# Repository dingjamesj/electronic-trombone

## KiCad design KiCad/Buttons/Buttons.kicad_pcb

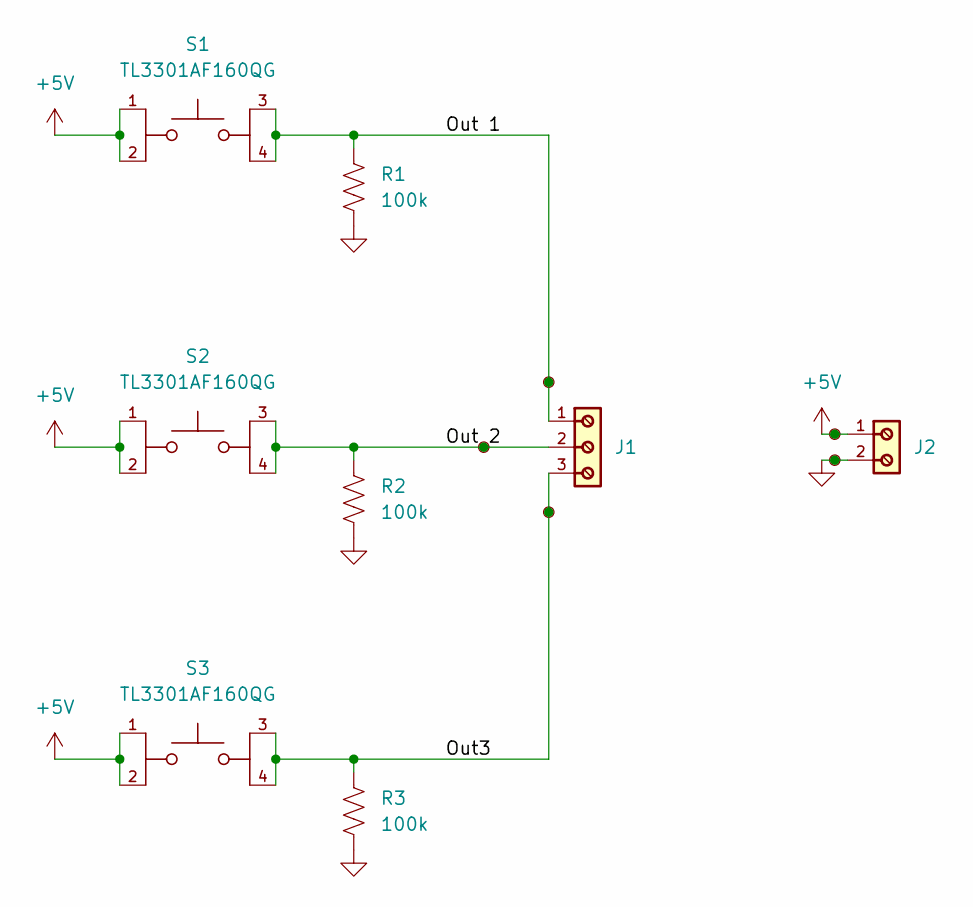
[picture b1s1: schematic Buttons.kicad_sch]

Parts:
J1: 691137710003
J2: 691137710002
R1, R2, R3: 100k; R_Axial_DIN0207_L6.3mm_D2.5mm_P7.62mm_Horizontal
S1, S2, S3: TL3301AF160QG; SW_TL3301AF160QG; PARTREV E
TP1, TP2, TP3, TP4, TP5: TestPoint_Small; TestPoint_Keystone_5000-5004_Miniature

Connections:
+5V: J2.1, S1.1, S1.2, S2.1, S2.2, S3.1, S3.2, TP2.1 (1_1)
/Out3: J1.3, R3.1, S3.3, S3.4, TP5.1 (1_1)
/Out 1: J1.1, R1.1, S1.3, S1.4, TP3.1 (1_1)
/Out 2: J1.2, R2.1, S2.3, S2.4, TP4.1 (1_1)
GND: J2.2, R1.2, R2.2, R3.2, TP1.1 (1_1)

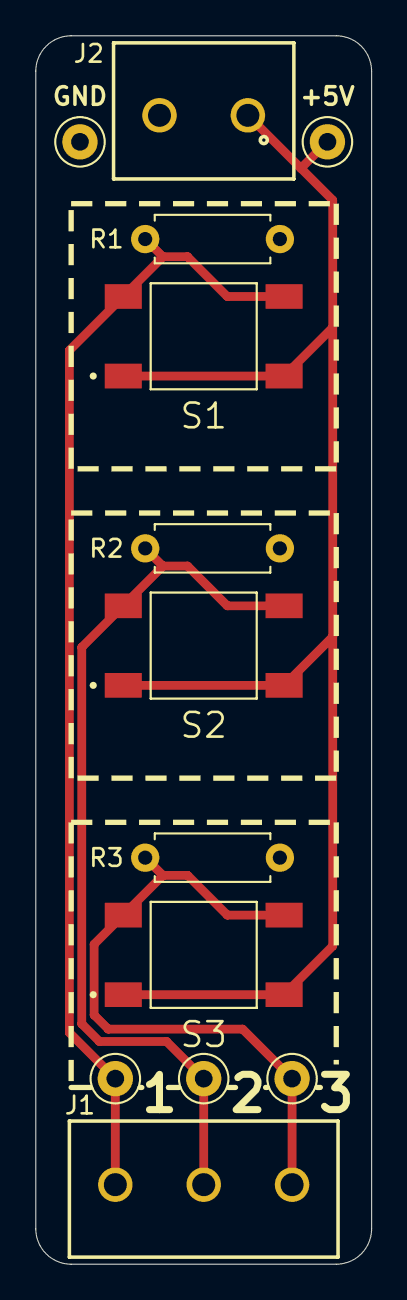
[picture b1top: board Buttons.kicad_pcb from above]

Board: 2 copper layers, 19.0 x 69.5 mm, 13 parts (0 on the bottom side), 5 nets.

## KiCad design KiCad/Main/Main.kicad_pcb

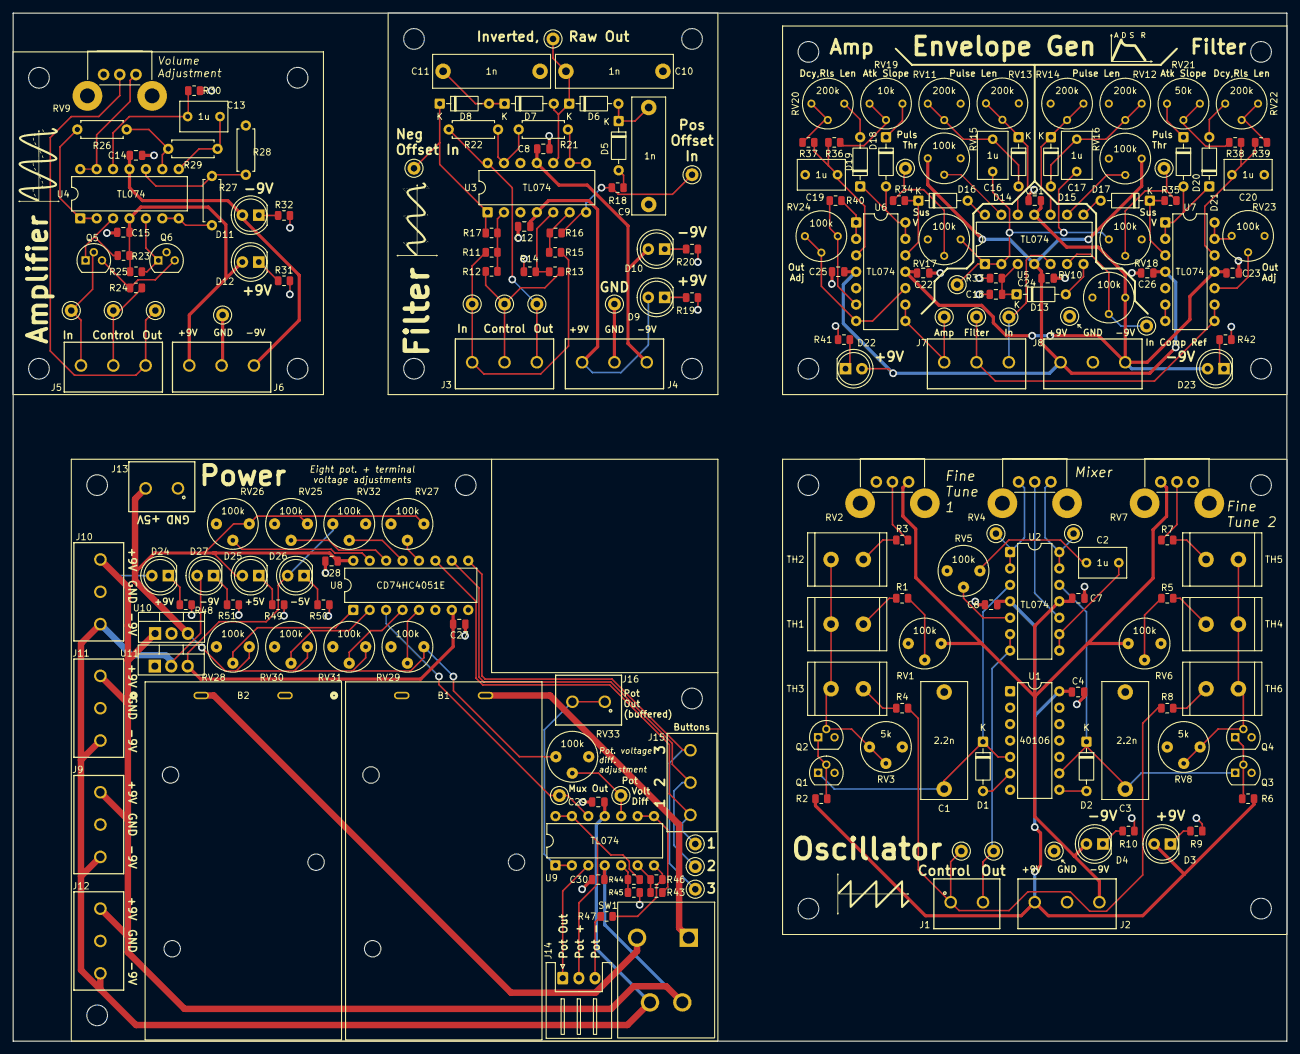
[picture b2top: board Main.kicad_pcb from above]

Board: 2 copper layers, 197.0 x 159.0 mm, 231 parts (0 on the bottom side), 127 nets.

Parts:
B1, B2: BC9VPC; BC9VPC_MPD
C1, C3: 2.2n; C_Rect_L18.0mm_W7.0mm_P15.00mm_FKS3_FKP3
C2, C13, C16, C17, C19, C20: 1u; C_Rect_L7.2mm_W4.5mm_P5.00mm
C4, C6, C7, C8, C12, C14, C15, C21, C22, C23, C24, C25, C26, C27, C28, C29, C30: 0.1u; C_0805_2012Metric
C9, C10, C11: 1n; C_Rect_L18.0mm_W5.0mm_P15.00mm_FKS3_FKP3
C18: 10n; C_0805_2012Metric
D1, D2, D5, D6, D7, D8, D13, D14, D15, D16, D17, D18, D19, D20, D21: 1N4148; D_DO-35_SOD27_P7.62mm_Horizontal
D3, D4, D9, D10, D11, D12, D22, D23, D24, D25, D26, D27: LED; LED_D5.0mm
H1, H2, H3, H4: MountingHole_3.2mm_M3
H5, H6, H7, H8, H9, H10, H11, H12, H13, H14, H15, H16, H17, H18, H19, H20: MountingHole; MountingHole_3.2mm_M3
J1, J13, J16: Screw_Terminal_01x02; 691137710002
J2, J3, J4, J5, J6, J7, J8, J9, J10, J11, J12, J15: Screw_Terminal_01x03; 691137710003
J14: Conn_01x03; JST_XH_S3B-XH-A_1x03_P2.50mm_Horizontal
Q1, Q3, Q5, Q6: NPN; TO-92
Q2, Q4: PNP; TO-92
R1, R4, R5, R8, R23, R25, R30, R33, R34, R35: 100k; R_0805_2012Metric
R2, R3, R6, R7: 1M; R_0805_2012Metric
R9, R10, R19, R20, R31, R32, R36, R41, R42, R47, R48, R51: 1k; R_0805_2012Metric
R11, R12, R13, R14, R15, R16, R17, R24, R43, R44, R45, R46: 10k; R_0805_2012Metric
R18: 2.2k; R_0805_2012Metric
R21, R28, R29: 10k; R_Axial_DIN0207_L6.3mm_D2.5mm_P7.62mm_Horizontal
R22: 1k; R_Axial_DIN0207_L6.3mm_D2.5mm_P7.62mm_Horizontal
R26, R27: 2.7k; R_Axial_DIN0207_L6.3mm_D2.5mm_P7.62mm_Horizontal
R37, R39, R40: 51k; R_0805_2012Metric
R38: 22k; R_0805_2012Metric
R49, R50: 820; R_0805_2012Metric
RV1, RV5, RV6, RV25, RV26, RV27, RV28, RV29, RV30, RV31, RV32, RV33: 100k; Potentiometer_Bourns_3339P_Vertical_HandSoldering
RV2, RV4, RV7, RV9: 100k; Potentiometer_Bourns_PTV09A-2_Single_Horizontal
RV3, RV8: 5k; Potentiometer_Bourns_3339P_Vertical_HandSoldering
RV10, RV15, RV16, RV17, RV18, RV23, RV24: 100k; Potentiometer_Bourns_3339P_Vertical
RV11, RV12, RV13, RV14, RV20, RV22: 200k; Potentiometer_Bourns_3339P_Vertical
RV19: 10k; Potentiometer_Bourns_3339P_Vertical
RV21: 50k; Potentiometer_Bourns_3339P_Vertical
SW1: SW_DPST; DPST Switch RA83231100
TH1, TH2, TH3, TH4, TH5, TH6: 10k; R_Radial_Power_L12.0mm_W8.0mm_P5.00mm
TP1, TP2, TP3, TP4, TP5, TP6, TP7, TP8, TP9, TP10, TP11, TP12, TP13, TP14, TP15, TP16, TP17, TP18, TP19, TP20, TP21, TP22, TP23, TP24, TP25, TP26, TP27, TP28, TP29: TestPoint_Small; TestPoint_Keystone_5000-5004_Miniature
U1: 40106; DIP-14_W7.62mm
U2, U3, U4, U5, U6, U7, U9: TL074; DIP-14_W7.62mm
U8: CD74HC4051E; DIP-16_W7.62mm
U10: L7805; TO-220-3_Vertical
U11: L7905; TO-220-3_Vertical

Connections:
+5V: C28.2, D25.2 (A), J13.2, RV25.1, RV26.1, RV27.1, RV28.1, RV29.1, RV30.1, RV31.1, RV33.3, U8.16 (VCC), U10.3 (OUT)
+9V: C4.1, C6.1, C12.2, C15.2, C24.2, C25.2, C26.2, C30.2, D3.2 (A), D9.2 (A), D11.2 (A), D22.2 (A), D24.2 (A), J2.1, J4.1, J6.1, J8.1, J9.1, J10.1, J11.1, J12.1, R2.1, R6.1, R23.1, R25.1, RV15.3, RV16.1, SW1.2, U1.14 (VDD), U2.4 (V+), U3.4 (V+), U4.4 (V+), U5.4 (V+), U6.4 (V+), U7.4 (V+), U9.4 (V+), U10.1 (IN)
-5V: C27.1, D26.2 (A), RV32.3, U8.7 (VEE), U11.3 (VO)
-9V: C7.2, C8.1, C14.1, C21.1, C22.1, C23.1, C29.1, D4.2 (A), D10.2 (A), D12.2 (A), D23.2 (A), D27.2 (A), J2.3, J4.3, J6.3, J8.3, J9.3, J10.3, J11.3, J12.3, RV1.1, RV2.1, RV6.3, RV7.3, RV10.1, SW1.4, U2.11 (V-), U3.11 (V-), U4.11 (V-), U5.11 (V-), U6.11 (V-), U7.11 (V-), U9.11 (V-), U11.2 (VI)
/Buffered Inverted Raw Out: R21.1, U3.8, U3.9 (-)
/Buffered Pot Out: J16.1, J16.2, U9.1, U9.2 (-)
/Button 1: J15.1, TP25.1 (1_1), U8.11 (S0)
/Button 2: J15.2, TP26.1 (1_1), U8.10 (S1)
/Button 3: J15.3, TP27.1 (1_1), U8.9 (S2)
/Control: J3.2, J5.2, R12.1, R13.2, R24.2, TP7.1 (1_1), TP14.1 (1_1)
/Envelope Generator/Amp Burst: D16.2 (A), U5.14
/Envelope Generator/Amp Out: J7.1, TP21.1 (1_1), U6.8, U6.9 (-)
/Envelope Generator/Amp Sustain/Base Voltage: R34.2, RV17.2, TP19.1 (1_1)
/Envelope Generator/Amp Target Voltage: D18.2 (A), D19.1 (K), U6.13 (-), U6.14
/Envelope Generator/Filter Burst: D17.2 (A), U5.8
/Envelope Generator/Filter Out: J7.2, TP22.1 (1_1), U7.8, U7.9 (-)
/Envelope Generator/Filter Sustain/Base Voltage: R35.2, RV18.2, TP20.1 (1_1)
/Envelope Generator/Filter Target Voltage: D20.2 (A), D21.1 (K), U7.1, U7.2 (-)
/Envelope Generator/In: J7.3, TP23.1 (1_1), U5.5 (+)
/Envelope Generator/Input Comparator Ref: RV10.2, TP17.1 (1_1), U5.6 (-)
/Envelope Generator/Normalized In: C16.1, C17.1, RV17.1, RV18.3, TP18.1 (1_1), U5.1, U5.2 (-)
/Envelope Generator/Unscaled Amp Out: R40.1, U6.1, U6.2 (-)
/Envelope Generator/Unscaled Filter Out: RV23.3, U7.13 (-), U7.14
/In: J3.1, J5.1, Q5.2 (B), R11.1, R15.1, TP6.1 (1_1), TP13.1 (1_1)
/Inverted Raw Out: C10.2, D6.1 (K), D7.2 (A), TP12.1 (1_1), U3.10 (+)
/Mux Out: TP28.1 (1_1), U8.3 (A), U9.12 (+)
/Oscillator/Control: J1.1, R4.1, R8.1, TP3.1 (1_1)
/Oscillator/Mix In 1: RV4.3, TP1.1 (1_1), U2.1, U2.2 (-)
/Oscillator/Mix In 2: RV4.1, TP2.1 (1_1), U2.13 (-), U2.14
/Oscillator/Out: J1.2, TP4.1 (1_1), U2.6 (-), U2.7
/Oscillator/Processed Control 1: Q2.2 (B), RV3.2, RV3.3, TH1.2, TH2.2, TH3.2
/Oscillator/Processed Control 2: Q4.2 (B), RV8.1, RV8.2, TH4.2, TH5.2, TH6.2
/Oscillator/Sch Inv In 1: C1.1, D1.1 (K), Q1.1 (C), U1.5, U2.3 (+)
/Oscillator/Sch Inv In 2: C3.1, D2.1 (K), Q3.1 (C), U1.9, U2.12 (+)
/Oscillator/Sch Inv Out 1: D1.2 (A), U1.6
/Oscillator/Sch Inv Out 2: D2.2 (A), U1.8
/Out: J3.3, J5.3, R22.2, RV9.2, TP8.1 (1_1), TP15.1 (1_1), U3.14
/Pot +: J14.2, R44.1, U9.13 (-), U9.14
/Pot -: J14.3, R47.2
/Pot Out: J14.1, U9.3 (+)
/Pot Voltage Difference: RV33.2, TP29.1 (1_1), U9.10 (+)
/Pot+ 1st Partial: RV25.2, U8.14 (A1)
/Pot+ 2nd Partial: RV26.2, U8.15 (A2)
/Pot+ 3rd Partial: RV27.2, U8.12 (A3)
/Pot+ 4th Partial: RV28.2, U8.1 (A4)
/Pot+ 5th Partial: RV29.2, U8.5 (A5)
/Pot+ 6th Partial: RV30.2, U8.2 (A6)
/Pot+ 7th Partial: RV31.2, U8.4 (A7)
/Pot+ Inactive: RV32.2, U8.13 (A0)
/Power/Thaw 3: U7.6 (-), U7.7
/Signal w. + Offset: R16.2, R18.1, TP10.1 (1_1), U3.7
/Signal w. - Offset: D8.1 (K), R17.2, TP11.1 (1_1), U3.1
GND: B1.1, B2.2, C1.2, C3.2, C4.2, C6.2, C7.1, C8.2, C9.1, C10.1, C11.1, C12.1, C14.2, C15.1, C18.2, C19.1, C20.1, C21.2, C22.2, C23.2, C24.1, C25.1, C26.1, C27.2, C28.1, C29.2, C30.1, J2.2, J4.2, J6.2, J8.2, J9.2, J10.2, J11.2, J12.2, J13.1, Q1.3 (E), Q2.3 (E), Q3.3 (E), Q4.3 (E), Q6.2 (B), R9.2, R10.2, R14.1, R19.2, R20.2, R28.2, R30.2, R31.2, R32.2, R33.2, R41.2, R42.2, R45.1, R48.2, R49.2, R50.2, R51.2, RV1.3, RV2.3, RV3.1, RV5.3, RV6.1, RV7.1, RV8.3, RV9.3, RV10.3, RV11.1, RV12.3, RV13.1, RV14.3, RV15.1, RV16.3, RV17.3, RV18.1, RV23.1, RV25.3, RV26.3, RV27.3, RV28.3, RV29.3, RV30.3, RV31.3, RV32.1, RV33.1, TP5.1 (1_1), TP9.1 (1_1), TP16.1 (1_1), TP24.1 (1_1), U1.1, U1.3, U1.7 (VSS), U1.11, U1.13, U3.3 (+), U3.12 (+), U6.5 (+), U7.5 (+), U8.6 (*E), U8.8 (GND), U10.2 (GND), U11.1 (GND)
unnamed: B1.2, SW1.1
unnamed: B2.1, SW1.3
unnamed: C2.2, RV5.1
unnamed: C13.1, R29.2, U4.8
unnamed: D3.1 (K), R9.1
unnamed: D4.1 (K), R10.1
unnamed: D5.2 (A), R18.2
unnamed: C9.2, D5.1 (K), D6.2 (A)
unnamed: C11.2, D7.1 (K), D8.2 (A)
unnamed: D9.1 (K), R19.1
unnamed: D10.1 (K), R20.1
unnamed: D11.1 (K), R31.1
unnamed: D12.1 (K), R32.1
unnamed: D13.2 (A), U5.7
unnamed: C18.1, D13.1 (K), R33.1, U5.3 (+)
unnamed: C16.2, D14.2 (A), RV11.2, RV11.3
unnamed: D14.1 (K), RV13.2, RV13.3, U5.12 (+)
unnamed: C17.2, D15.2 (A), RV12.1, RV12.2
unnamed: D15.1 (K), RV14.1, RV14.2, U5.10 (+)
unnamed: D16.1 (K), R34.1, U6.12 (+)
unnamed: D17.1 (K), R35.1, U7.3 (+)
unnamed: D18.1 (K), RV19.1
unnamed: D19.2 (A), RV20.1
unnamed: D20.1 (K), RV21.3
unnamed: D21.2 (A), RV22.3
unnamed: D22.1 (K), R41.1
unnamed: D23.1 (K), R42.1
unnamed: D24.1 (K), R48.1
unnamed: D25.1 (K), R49.1
unnamed: D26.1 (K), R50.1
unnamed: D27.1 (K), R51.1
unnamed: Q1.2 (B), Q2.1 (C), R2.2
unnamed: Q3.2 (B), Q4.1 (C), R6.2
unnamed: Q5.1 (C), R23.2, U4.3 (+)
unnamed: Q5.3 (E), Q6.3 (E), R24.1
unnamed: Q6.1 (C), R25.2, U4.5 (+)
unnamed: R1.1, RV1.2
unnamed: R1.2, TH1.1
unnamed: R3.1, RV2.2
unnamed: R3.2, TH2.1
unnamed: R4.2, TH3.1
unnamed: R5.1, RV6.2
unnamed: R5.2, TH4.1
unnamed: R7.1, RV7.2
unnamed: R7.2, TH5.1
unnamed: R8.2, TH6.1
unnamed: R36.1, RV19.2, RV19.3
unnamed: R37.1, RV20.2, RV20.3
unnamed: R38.1, RV21.1, RV21.2
unnamed: R39.1, RV22.1, RV22.2
unnamed: R46.2, R47.1, U9.7
unnamed: RV5.2, U2.5 (+)
unnamed: RV4.2, U2.10 (+)
unnamed: C2.1, U2.8, U2.9 (-)
unnamed: R11.2, R12.2, R17.1, U3.2 (-)
unnamed: R13.1, R14.2, U3.5 (+)
unnamed: R15.2, R16.1, U3.6 (-)
unnamed: R21.2, R22.1, U3.13 (-)
unnamed: R26.1, U4.1, U4.2 (-)
unnamed: R27.1, U4.6 (-), U4.7
unnamed: R27.2, R28.1, U4.10 (+)
unnamed: R26.2, R29.1, U4.9 (-)
unnamed: C13.2, R30.1, U4.12 (+)
unnamed: RV9.1, U4.13 (-), U4.14
unnamed: RV16.2, U5.9 (-)
unnamed: RV15.2, U5.13 (-)
unnamed: C19.2, R36.2, R37.2, U6.3 (+)
unnamed: R40.2, RV24.1, U6.6 (-)
unnamed: RV24.2, RV24.3, U6.7, U6.10 (+)
unnamed: RV23.2, U7.10 (+)
unnamed: C20.2, R38.2, R39.2, U7.12 (+)
unnamed: R44.2, R45.2, U9.5 (+)
unnamed: R43.2, R46.1, U9.6 (-)
unnamed: R43.1, U9.8, U9.9 (-)

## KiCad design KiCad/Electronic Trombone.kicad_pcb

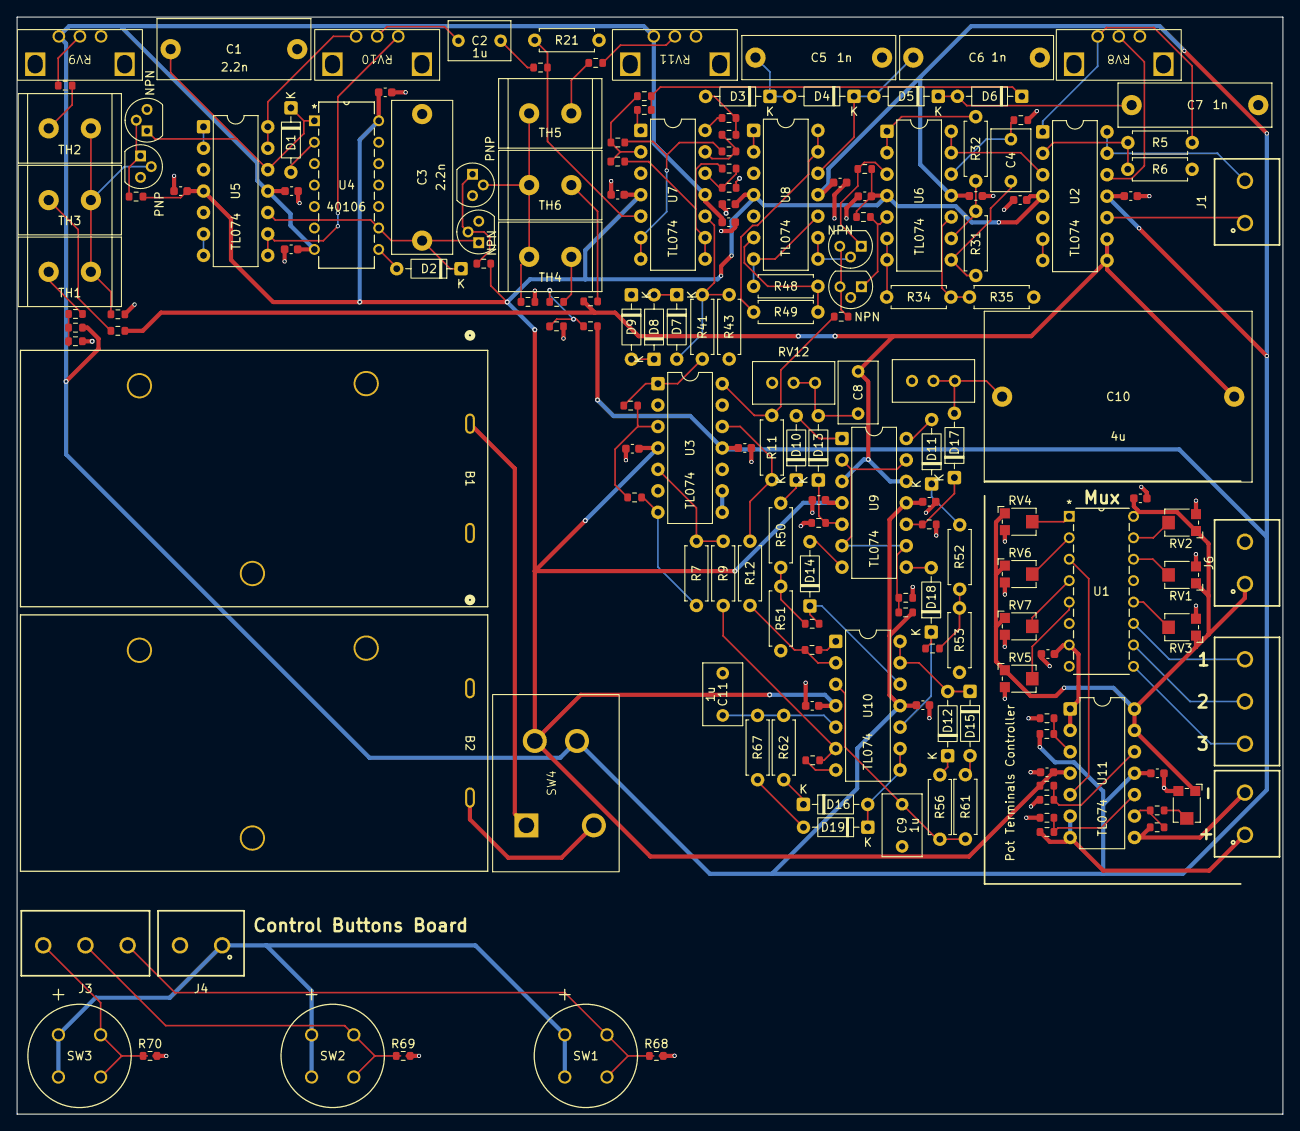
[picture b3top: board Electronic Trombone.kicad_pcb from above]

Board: 2 copper layers, 150.0 x 130.0 mm, 173 parts (0 on the bottom side), 124 nets.

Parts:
B1, B2: BC9VPC; BC9VPC_MPD
C1, C3: 2.2n; C_Rect_L18.0mm_W7.0mm_P15.00mm_FKS3_FKP3
C2, C4, C8, C9, C11: 1u; C_Rect_L7.2mm_W4.5mm_P5.00mm
C5, C6, C7: 1n; C_Rect_L18.0mm_W5.0mm_P15.00mm_FKS3_FKP3
C10: 4u; C_Rect_L31.5mm_W20.0mm_P27.50mm_MKS4
C12, C13, C14, C15, C16, C17, C18, C19, C20, C21, C22, C23, C24, C25, C26, C27, C28, C29, C30, C31, C32, C33: 0.1u; C_0603_1608Metric
D1, D2, D3, D4, D5, D6, D7, D8, D9, D10, D11, D12, D13, D14, D15, D16, D17, D18, D19: 1N4148; D_DO-35_SOD27_P7.62mm_Horizontal
J1, J4, J5, J6: 691137710002
J2, J3: 691137710003
Q1, Q3, Q5, Q6: NPN; TO-92
Q2, Q4: PNP; TO-92
R1, R2, R3, R4, R8, R10, R36: 10k; R_0603_1608Metric
R5, R6, R7, R9, R11, R12, R21, R31, R32, R34, R35, R41, R43, R48, R49, R50, R51, R52, R53, R56, R61, R62, R67: R_US; R_Axial_DIN0207_L6.3mm_D2.5mm_P7.62mm_Horizontal
R13, R15, R22, R24, R37, R38, R40, R42, R44, R45, R47, R58, R59, R64, R65, R68, R69, R70: 30k; R_0603_1608Metric
R14, R18, R20, R23, R27, R29, R30, R33, R54, R55: 100k; R_0603_1608Metric
R16, R17, R25, R26: 1M; R_0603_1608Metric
R19, R28: 2.4k; R_0603_1608Metric
R39, R46, R60, R66: 1k; R_0603_1608Metric
R71, R74: 15k; R_0603_1608Metric
R72, R73: 12k; R_0603_1608Metric
RV1, RV2, RV3, RV4, RV5, RV6, RV7, RV14: 20k; Potentiometer_Bourns_TC33X_Vertical
RV8, RV9, RV10, RV11: 100k; Potentiometer 100k PTV09A-2020F-B104
RV12: 100k; Potentiometer_Bourns_3296W_Vertical
RV13: 1M; Potentiometer_Bourns_3296W_Vertical
SW1, SW2, SW3: D6R90F2LFS; D6R90_CNK
SW4: SW_DPST; DPST Switch RA83231100
TH1, TH2, TH3, TH4, TH5, TH6: 10k; R_Radial_Power_L12.0mm_W8.0mm_P5.00mm
U1: CD74HC4051E; N16
U2, U3, U5, U6, U7, U8, U9, U10, U11: TL074; DIP-14_W7.62mm
U4: 40106; N14

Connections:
+5V: C32.2, J4.1, J6.1, RV1.1, RV2.1, RV3.1, RV4.1, RV5.1, RV6.1, RV7.1, RV14.1, SW1.1, SW1.4, SW2.1, SW2.4, SW3.1, SW3.4, U1.16 (VCC), U11.13 (-), U11.14
+9V: C12.1, C14.1, C16.1, C18.1, C20.1, C22.1, C24.1, C26.1, C28.1, C30.1, R16.1, R25.1, R29.1, R30.1, R72.2, SW4.2, U2.4 (V+), U3.4 (V+), U4.14 (VDD), U5.4 (V+), U6.4 (V+), U7.4 (V+), U8.4 (V+), U9.4 (V+), U10.4 (V+), U11.4 (V+)
-5V: C33.1, U1.7 (VEE), U11.1, U11.2 (-)
-9V: C13.2, C15.2, C17.2, C19.2, C21.2, C23.2, C25.2, C27.2, C29.2, C31.2, R15.1, R24.1, R55.2, R73.1, RV9.3, RV11.3, SW4.4, U2.11 (V-), U3.11 (V-), U4.7 (VSS), U5.11 (V-), U6.11 (V-), U7.11 (V-), U8.11 (V-), U9.11 (V-), U10.11 (V-), U11.11 (V-)
//Amp Control: R11.2, R36.2, U3.14
//Amplifier/Out: U2.3 (+), U6.13 (-), U6.14
//Amplifier/Signal In: Q5.2 (B), U8.8, U8.9 (-)
//Audio Control: J1.1, U2.10 (+)
//Audio Out: J1.2, U2.13 (-), U2.14
//Buffered Audio Control: C8.1, C10.1, R18.1, R27.1, U2.8, U2.9 (-), U9.3 (+), U9.12 (+)
//Envelope Generator/Amp Sustain Voltage: R50.2, R51.1, R59.2
//Envelope Generator/Filter Sustain Voltage: R52.2, R53.1, R65.2
//Envelope Generator/Out Amp: R12.1, R60.2, U10.2 (-)
//Envelope Generator/Out Filter: R9.1, R66.2, U10.6 (-)
//Envelope Generator/Trigger Ref: R54.2, R55.1, U9.2 (-), U9.6 (-), U9.9 (-), U9.13 (-)
//Filter Control: R8.2, R41.2, U3.1
//Filter/Processed Control: R40.2, R47.1, U7.8, U7.9 (-)
//Filter/Signal In: R38.1, R45.1, U7.6 (-), U7.7
//Filter/Signal In w. +Offset: D3.2 (A), R37.2, R39.1
//Filter/Signal In w. -Offset: D6.1 (K), R44.2, R46.1
//Filter/Unprocessed Out: C6.2, D4.1 (K), D5.2 (A), U8.12 (+)
//Oscillator/Core In 1: Q2.2 (B), R19.1, TH1.2, TH2.2, TH3.2
//Oscillator/Core In 2: Q4.2 (B), R28.1, TH4.2, TH5.2, TH6.2
//Oscillator/Mix In 1: RV10.3, U5.13 (-), U5.14
//Oscillator/Mix In 2: RV10.1, U5.8, U5.9 (-)
//Oscillator/Sch Inv In 1: C1.1, D1.1 (K), Q1.1 (C), U4.1, U5.12 (+)
//Oscillator/Sch Inv In 2: C3.1, D2.1 (K), Q3.1 (C), U4.9, U5.10 (+)
//Oscillator/Sch Inv Out 1: D1.2 (A), U4.2
//Oscillator/Sch Inv Out 2: D2.2 (A), U4.8
//Oscillator/Tuning 1: R17.1, RV9.2
//Oscillator/Tuning 2: R26.1, RV11.2
/Custom Potentiometer Controls/+Pot: J5.1, R2.1, U11.6 (-), U11.7
/Custom Potentiometer Controls/+Pot 1st Partial: RV1.2, U1.14 (A1)
/Custom Potentiometer Controls/+Pot 2nd Partial: RV2.2, U1.15 (A2)
/Custom Potentiometer Controls/+Pot 3rd Partial: RV3.2, U1.12 (A3)
/Custom Potentiometer Controls/+Pot 4th Partial: RV4.2, U1.1 (A4)
/Custom Potentiometer Controls/+Pot 5th Partial: RV5.2, U1.5 (A5)
/Custom Potentiometer Controls/+Pot 6th Partial: RV6.2, U1.2 (A6)
/Custom Potentiometer Controls/+Pot 7th Partial: RV7.2, U1.4 (A7)
/Custom Potentiometer Controls/-Pot: J5.2, R3.2, U11.8
/Custom Potentiometer Controls/Mux Out: U1.3 (A), U11.5 (+)
/Custom Potentiometer Controls/Pot Voltage Difference: R1.1, RV14.2
/Custom Potentiometer Controls/Trigger 1: J2.3, U1.11 (S0)
/Custom Potentiometer Controls/Trigger 2: J2.2, U1.10 (S1)
/Custom Potentiometer Controls/Trigger 3: J2.1, U1.9 (S2)
/Power/Thaw 2: U2.6 (-), U2.7
/Power/Thaw 3: U3.8, U3.9 (-)
/Power/Thaw 5C: U5.1, U5.2 (-)
/Power/Thaw 5D: U5.6 (-), U5.7
/Power/Thaw 8: U8.1, U8.2 (-)
GND: B1.2, B2.1, C1.2, C3.2, C5.1, C6.1, C7.1, C9.1, C11.1, C12.2, C13.1, C14.2, C15.1, C16.2, C17.1, C18.2, C19.1, C20.2, C21.1, C22.2, C23.1, C24.2, C25.1, C26.2, C27.1, C28.2, C29.1, C30.2, C31.1, C32.1, C33.2, D9.1 (K), J4.2, J6.2, Q1.3 (E), Q2.3 (E), Q3.3 (E), Q4.3 (E), Q6.2 (B), R4.1, R6.1, R13.2, R19.2, R21.1, R22.2, R28.2, R33.2, R35.2, R42.1, R43.1, R51.2, R53.2, R54.1, R58.2, R64.2, R68.2, R69.2, R70.2, R71.2, R74.1, RV1.3, RV2.3, RV3.3, RV4.3, RV5.3, RV6.3, RV7.3, RV8.1, RV9.1, RV11.1, RV12.3, RV13.3, RV14.3, U1.6 (*E), U1.8 (GND), U1.13 (A0), U2.5 (+), U3.2 (-), U3.6 (-), U3.10 (+), U3.13 (-), U4.3, U4.5, U4.11, U4.13, U5.3 (+), U5.5 (+), U7.3 (+), U8.3 (+), U8.5 (+)
unnamed: B1.1, SW4.1
unnamed: B2.2, SW4.3
unnamed: C2.1, RV10.2
unnamed: C2.2, R20.1
unnamed: C4.1, R31.2, U6.8
unnamed: C5.2, D3.1 (K), D4.2 (A)
unnamed: C7.2, D5.1 (K), D6.2 (A)
unnamed: D7.2 (A), R41.1, R43.2, U7.10 (+)
unnamed: D7.1 (K), D8.2 (A)
unnamed: D8.1 (K), D9.2 (A)
unnamed: D10.2 (A), U9.1
unnamed: D10.1 (K), R50.1
unnamed: D11.2 (A), U9.14
unnamed: D11.1 (K), R52.1
unnamed: D12.2 (A), D15.1 (K), U10.13 (-), U10.14
unnamed: D12.1 (K), R56.1
unnamed: C8.2, D13.2 (A), RV12.1, RV12.2
unnamed: D13.1 (K), R58.1, U9.5 (+)
unnamed: D14.2 (A), U9.7
unnamed: D14.1 (K), R59.1, U10.12 (+)
unnamed: D15.2 (A), R61.1
unnamed: D16.2 (A), D19.1 (K), U10.8, U10.9 (-)
unnamed: D16.1 (K), R62.1
unnamed: C10.2, D17.2 (A), RV13.1, RV13.2
unnamed: D17.1 (K), R64.1, U9.10 (+)
unnamed: D18.2 (A), U9.8
unnamed: D18.1 (K), R65.1, U10.10 (+)
unnamed: D19.2 (A), R67.1
unnamed: J3.1, R68.1, SW1.2, SW1.3
unnamed: J3.2, R69.1, SW2.2, SW2.3
unnamed: J3.3, R70.1, SW3.2, SW3.3
unnamed: Q1.2 (B), Q2.1 (C), R16.2
unnamed: Q3.2 (B), Q4.1 (C), R25.2
unnamed: Q5.1 (C), R29.2, U6.3 (+)
unnamed: Q5.3 (E), Q6.3 (E), R36.1
unnamed: Q6.1 (C), R30.2, U6.5 (+)
unnamed: R5.2, RV8.3, U2.1
unnamed: R7.2, R10.1, U3.7
unnamed: R13.1, R14.1, R15.2
unnamed: R14.2, TH1.1
unnamed: R17.2, TH2.1
unnamed: R18.2, TH3.1
unnamed: R22.1, R23.1, R24.2
unnamed: R23.2, TH4.1
unnamed: R26.2, TH5.1
unnamed: R27.2, TH6.1
unnamed: R39.2, U7.14
unnamed: R46.2, U7.1
unnamed: R60.1, U10.1
unnamed: R66.1, U10.7
unnamed: R5.1, R6.2, U2.2 (-)
unnamed: RV8.2, U2.12 (+)
unnamed: R8.1, R10.2, U3.3 (+)
unnamed: R7.1, R9.2, U3.5 (+)
unnamed: R11.1, R12.2, U3.12 (+)
unnamed: R32.1, U6.1, U6.2 (-)
unnamed: R34.1, U6.6 (-), U6.7
unnamed: R34.2, R35.1, U6.10 (+)
unnamed: R31.1, R32.2, U6.9 (-)
unnamed: C4.2, R33.1, U6.12 (+)
unnamed: R44.1, R45.2, R47.2, U7.2 (-)
unnamed: R20.2, R21.2, U7.5 (+)
unnamed: R40.1, R42.2, U7.12 (+)
unnamed: R37.1, R38.2, U7.13 (-)
unnamed: R48.1, R49.2, U8.6 (-)
unnamed: R48.2, U8.7, U8.10 (+)
unnamed: R49.1, U8.13 (-), U8.14
unnamed: C9.2, R56.2, R61.2, U10.3 (+)
unnamed: C11.2, R62.2, R67.2, U10.5 (+)
unnamed: R71.1, R73.2, U11.3 (+)
unnamed: R2.2, R4.2, U11.10 (+)
unnamed: R1.2, R3.1, U11.9 (-)
unnamed: R72.1, R74.2, U11.12 (+)

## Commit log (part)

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2026-05-22 re-initalize project as KiCad project
2026-05-27 completed oscillator schematic
2026-05-27 reorganized project files
2026-06-02 uploaded files from my Windows file system
2026-06-02 added resistor values to the osc.'s amp. cct.
2026-06-05 updated spice simulation
2026-06-08 added power supply pcb
2026-06-08 removed MCU testing folder from repo
2026-06-08 added mixer into circuit
2026-06-09 removed unnecessary buffers in front of each osc.
    Also put LTspice simulation files in their own folder
2026-06-09 same as prev. commit
2026-06-11 unified kicad projects, added footprints
2026-06-11 renamed main schematic file, annotations start at 0
2026-06-11 SPICE simulation now uses 9V instead of 12V
2026-06-13 amplifier sch., general changes to oscillator sch.
2026-06-14 improved osc.'s output buffer cct., swap filter & amp
2026-06-14 made filter's core, but not CV and output ccts.
2026-06-14 added critical trimmer resistor that the osc. was missing
    The trimmer resistor serves in a voltage divider to the osc.'s input signal. Without that voltage divider, the coarse tuning knob's range is too large (i.e. it's too coarse) and therefore unusable (a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
2026-06-14 drafted filter schematic
2026-06-14 drafted a dual output envelope generator
2026-06-14 renamed "SPICE simulation.asc" to "Oscillator.asc"
2026-06-20 replaced some pots with voltage dividers, ltspice qol
2026-06-20 created SPICE sim for Voltage Controlled Filter
2026-06-21 drafted envelope generator LTspice simulation
2026-06-21 adjusted values of the envelope generator
2026-06-21 drafted voltage controlled amplifier SPICE sim.
2026-06-22 wrote ac analysis for filter, stepping through CVs
    I was trying to find the relationship between the filter's cutoff frequency and the its control voltage. As it turns out, the relationship is exponential (i.e. a linear increase in CV results in an e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
2026-06-23 created a symbol for the filter
2026-06-23 gave symbols to the remaining schematics
2026-06-24 created (near) total cct. SPICE simulation
2026-06-24 fixed filter cct to output 10mV pp
2026-06-24 adjusted envelope generator values in LTspice
2026-06-26 finalizing schematic
2026-06-29 updated footprints
2026-06-29 added potentiometer voltage control cct
2026-06-29 added push button footprints
2026-06-29 renamed button controls schematic file
2026-06-29 added volume control knob
2026-06-30 added power switch, decoupling caps, and unused IC pins
